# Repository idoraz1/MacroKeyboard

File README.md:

# Ido's macro-keyboard
here is the final results - iv'e done 1to1 as in the tutorial to keep it simple and easy.

### Inspiration

I wanted to create a macropad that would help me in my coding and 3D modeling. i needed something that will help me with copy and pasting. and i also remembered how many mistakes i do, so i had to added the undo and redo buttons! I created a macropad using 4 switches, 1 rp2040, and 2 leds. 

### Challenges

following the Fusion tutorial was a struggle. i did everything twice before making it good. but in the end the results are great.

### Specifications

BOM: 
- 4x Cherry MX Switches
- 2x SK6812 MINI Leds
- 1x XIAO RP2040
- 4x Blank DSA Keycaps
- 4x M3x16 Bolt
- 4x M3 Heatset

Others:
- KMK Firmware ( python ) 
- Top Case
- Bottom Case 

Schematic            |  PCB
:-------------------------:|:-------------------------:|
  |  

Base            |  Case
:-------------------------:|:-------------------------:|
  |

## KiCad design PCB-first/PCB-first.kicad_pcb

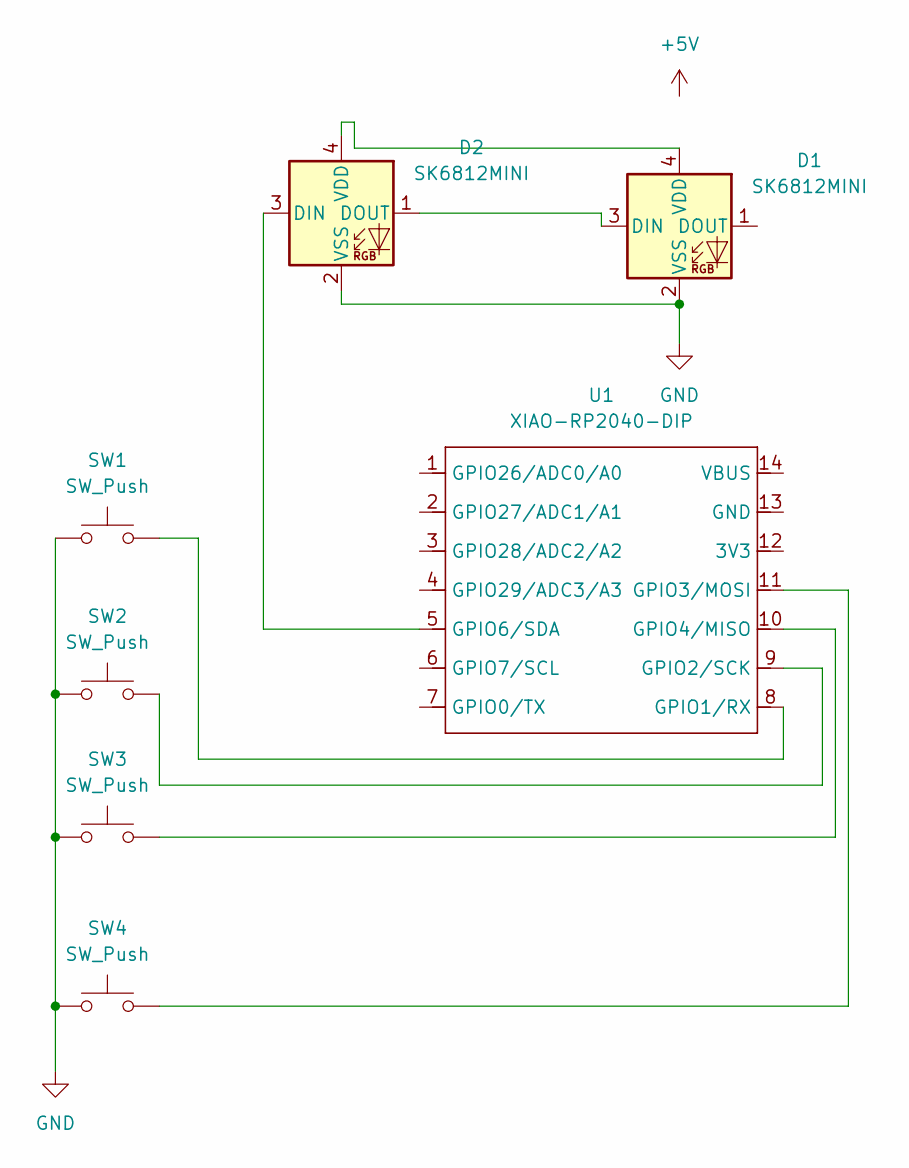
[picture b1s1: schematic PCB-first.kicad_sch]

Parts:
D1, D2: SK6812MINI; LED_SK6812MINI_PLCC4_3.5x3.5mm_P1.75mm
SW1, SW2, SW3, SW4: SW_Push; SW_Cherry_MX_1.00u_PCB
U1: XIAO-RP2040-DIP

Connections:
+5V: D1.4 (VDD), D2.4 (VDD)
GND: D1.2 (VSS), D2.2 (VSS), SW1.1, SW2.1, SW3.1, SW4.1
unnamed: D1.3 (DIN), D2.1 (DOUT)
unnamed: D2.3 (DIN), U1.5 (GPIO6/SDA)
unnamed: SW1.2, U1.8 (GPIO1/RX)
unnamed: SW2.2, U1.9 (GPIO2/SCK)
unnamed: SW4.2, U1.11 (GPIO3/MOSI)
unnamed: SW3.2, U1.10 (GPIO4/MISO)

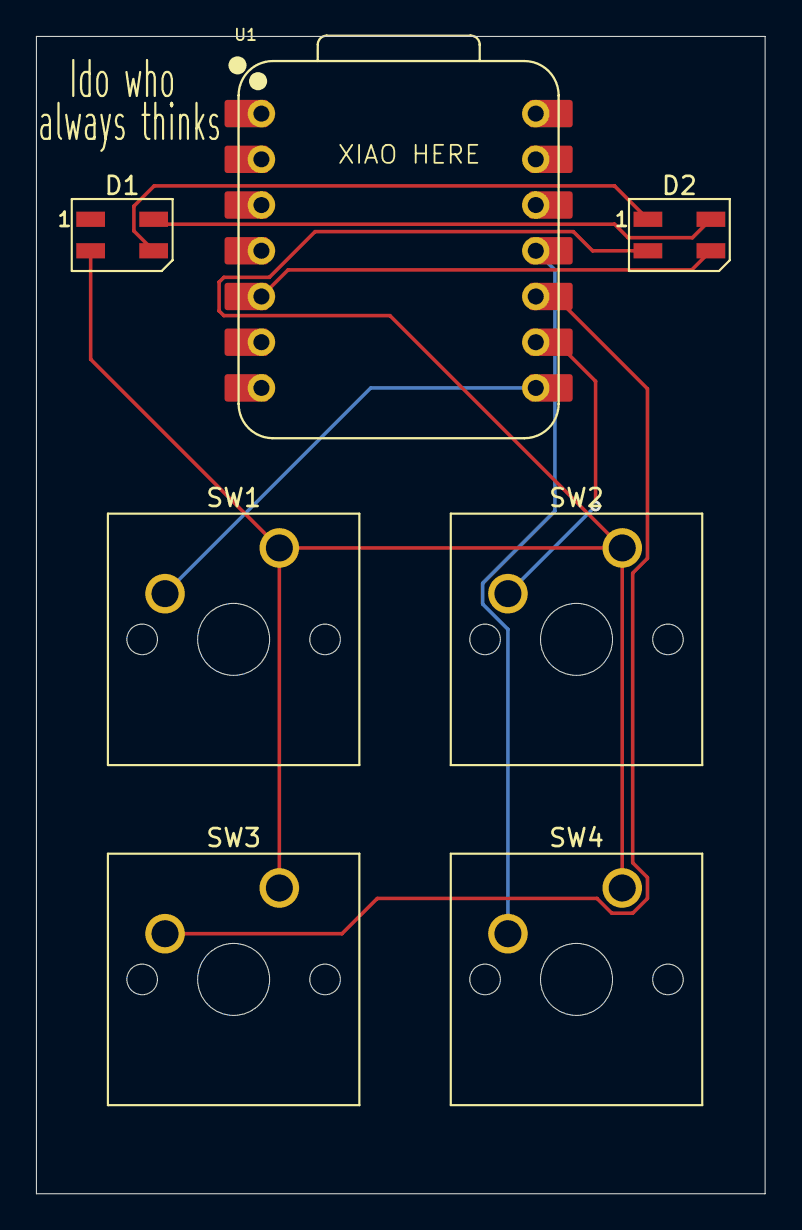
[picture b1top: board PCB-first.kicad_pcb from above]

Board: 2 copper layers, 40.5 x 64.3 mm, 7 parts (0 on the bottom side), 8 nets.

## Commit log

2025-11-29 Added all the folders for this project
    iv'e added the CAD, PCB(FIRST),FIRMWARE folders which contains all the files we need for this keyboard.
2025-11-29 fixed 5v net
2025-11-29 Created README.md
